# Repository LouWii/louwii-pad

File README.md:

# Louwii Pad

**Very basic USB macro pad for tinkering and experimenting.**

The main goal is to have it run a custom [QMK](https://docs.qmk.fm/) firmware, so that it can be easily programmed to be used as a macropad to help with day to day tasks. As it's running an ATmega32u4, same as the Arduino Leonardo & Micro, it can be programmed through the Arduino IDE as well, for even more customization.

![louwii-pad-rev1-small](https://private-user-images.githubusercontent.com/2750789/670247439-dfbe5354-9f28-458f-8513-f5d79d3b1d79.jpeg?jwt=eyJ0eXAiOiJKV1QiLCJhbGciOiJIUzI1NiJ9.eyJpc3MiOiJnaXRodWIuY29tIiwiYXVkIjoicmF3LmdpdGh1YnVzZXJjb250ZW50LmNvbSIsImtleSI6ImtleTUiLCJleHAiOjE3OTE2MDY3MzIsIm5iZiI6MTc5MTYwNjQzMiwicGF0aCI6Ii8yNzUwNzg5LzY3MDI0NzQzOS1kZmJlNTM1NC05ZjI4LTQ1OGYtODUxMy1mNWQ3OWQzYjFkNzkuanBlZz9YLUFtei1BbGdvcml0aG09QVdTNC1ITUFDLVNIQTI1NiZYLUFtei1DcmVkZW50aWFsPUFLSUFWQ09EWUxTQTUzUFFLNFpBJTJGMjAyNjEwMTAlMkZ1cy1lYXN0LTElMkZzMyUyRmF3czRfcmVxdWVzdCZYLUFtei1EYXRlPTIwMjYxMDEwVDA0MjcxMlomWC1BbXotRXhwaXJlcz0zMDAmWC1BbXotU2lnbmF0dXJlPTJkZTdlY2E2MmEyYmFmMzFiNmU4NDI2MTk5MDRmYjJjY2RkNmYwZjc5OTA3MTJlYjgzNDFjMWMxNGFiNTI4MTAmWC1BbXotU2lnbmVkSGVhZGVycz1ob3N0JnJlc3BvbnNlLWNvbnRlbnQtdHlwZT1pbWFnZSUyRmpwZWcifQ.r9Crihq03SLz5WYOTDRxo0ubDbzw7JnOoz72aCsSmFU)

![louwii-pad-rev1-demo](https://private-user-images.githubusercontent.com/2750789/670255763-4d714bb6-b55f-40b0-9e51-5dd4ab754735.gif?jwt=eyJ0eXAiOiJKV1QiLCJhbGciOiJIUzI1NiJ9.eyJpc3MiOiJnaXRodWIuY29tIiwiYXVkIjoicmF3LmdpdGh1YnVzZXJjb250ZW50LmNvbSIsImtleSI6ImtleTUiLCJleHAiOjE3OTE2MDgxOTMsIm5iZiI6MTc5MTYwNzg5MywicGF0aCI6Ii8yNzUwNzg5LzY3MDI1NTc2My00ZDcxNGJiNi1iNTVmLTQwYjAtOWU1MS01ZGQ0YWI3NTQ3MzUuZ2lmP1gtQW16LUFsZ29yaXRobT1BV1M0LUhNQUMtU0hBMjU2JlgtQW16LUNyZWRlbnRpYWw9QUtJQVZDT0RZTFNBNTNQUUs0WkElMkYyMDI2MTAxMCUyRnVzLWVhc3QtMSUyRnMzJTJGYXdzNF9yZXF1ZXN0JlgtQW16LURhdGU9MjAyNjEwMTBUMDQ1MTMzWiZYLUFtei1FeHBpcmVzPTMwMCZYLUFtei1TaWduYXR1cmU9ZWU5ZTIwNDVjZWY1OTQwN2Y3YzA2Nzk1MTAyMDU3NDMxMTI2N2RiNjA0Zjg4YjAwZTJkOWJiYTJjMjczZDJmOSZYLUFtei1TaWduZWRIZWFkZXJzPWhvc3QmcmVzcG9uc2UtY29udGVudC10eXBlPWltYWdlJTJGZ2lmIn0.mEn1UY_JDH-Clc5-bU8d7kEX9qx5xtZxYkt8m8s8BgE)

This demo is running the default QMK firmware. The bottom right knob is used to switch between layers, which get displayed on the OLED screen.

## Inspiration

* [ruiqimao's tutorial](https://github.com/ruiqimao/keyboard-pcb-guide)
* [Arisu](https://github.com/FateNozomi/arisu-pcb)
* [cpm43](https://github.com/Gtrx0/cpm43)
* [Gtrx0/Keyboard-template-atmega32u4](https://github.com/Gtrx0/Keyboard-template-atmega32u4)

[ATmega32u4 official doc](http://ww1.microchip.com/downloads/en/devicedoc/atmel-7766-8-bit-avr-atmega16u4-32u4_datasheet.pdf)

## BOM (list of components)

[See doc](BOM.md)

## Bootlader, ATmega flashing

Flash a bootloader, set the chip fuses: [See doc](ATMEGA.md)

## Firmware (QMK)

[See doc](FIRMWARE.md)

## Revisions

[See doc](REVISIONS.md)

## Third party libs

[See doc](LIBS.md)

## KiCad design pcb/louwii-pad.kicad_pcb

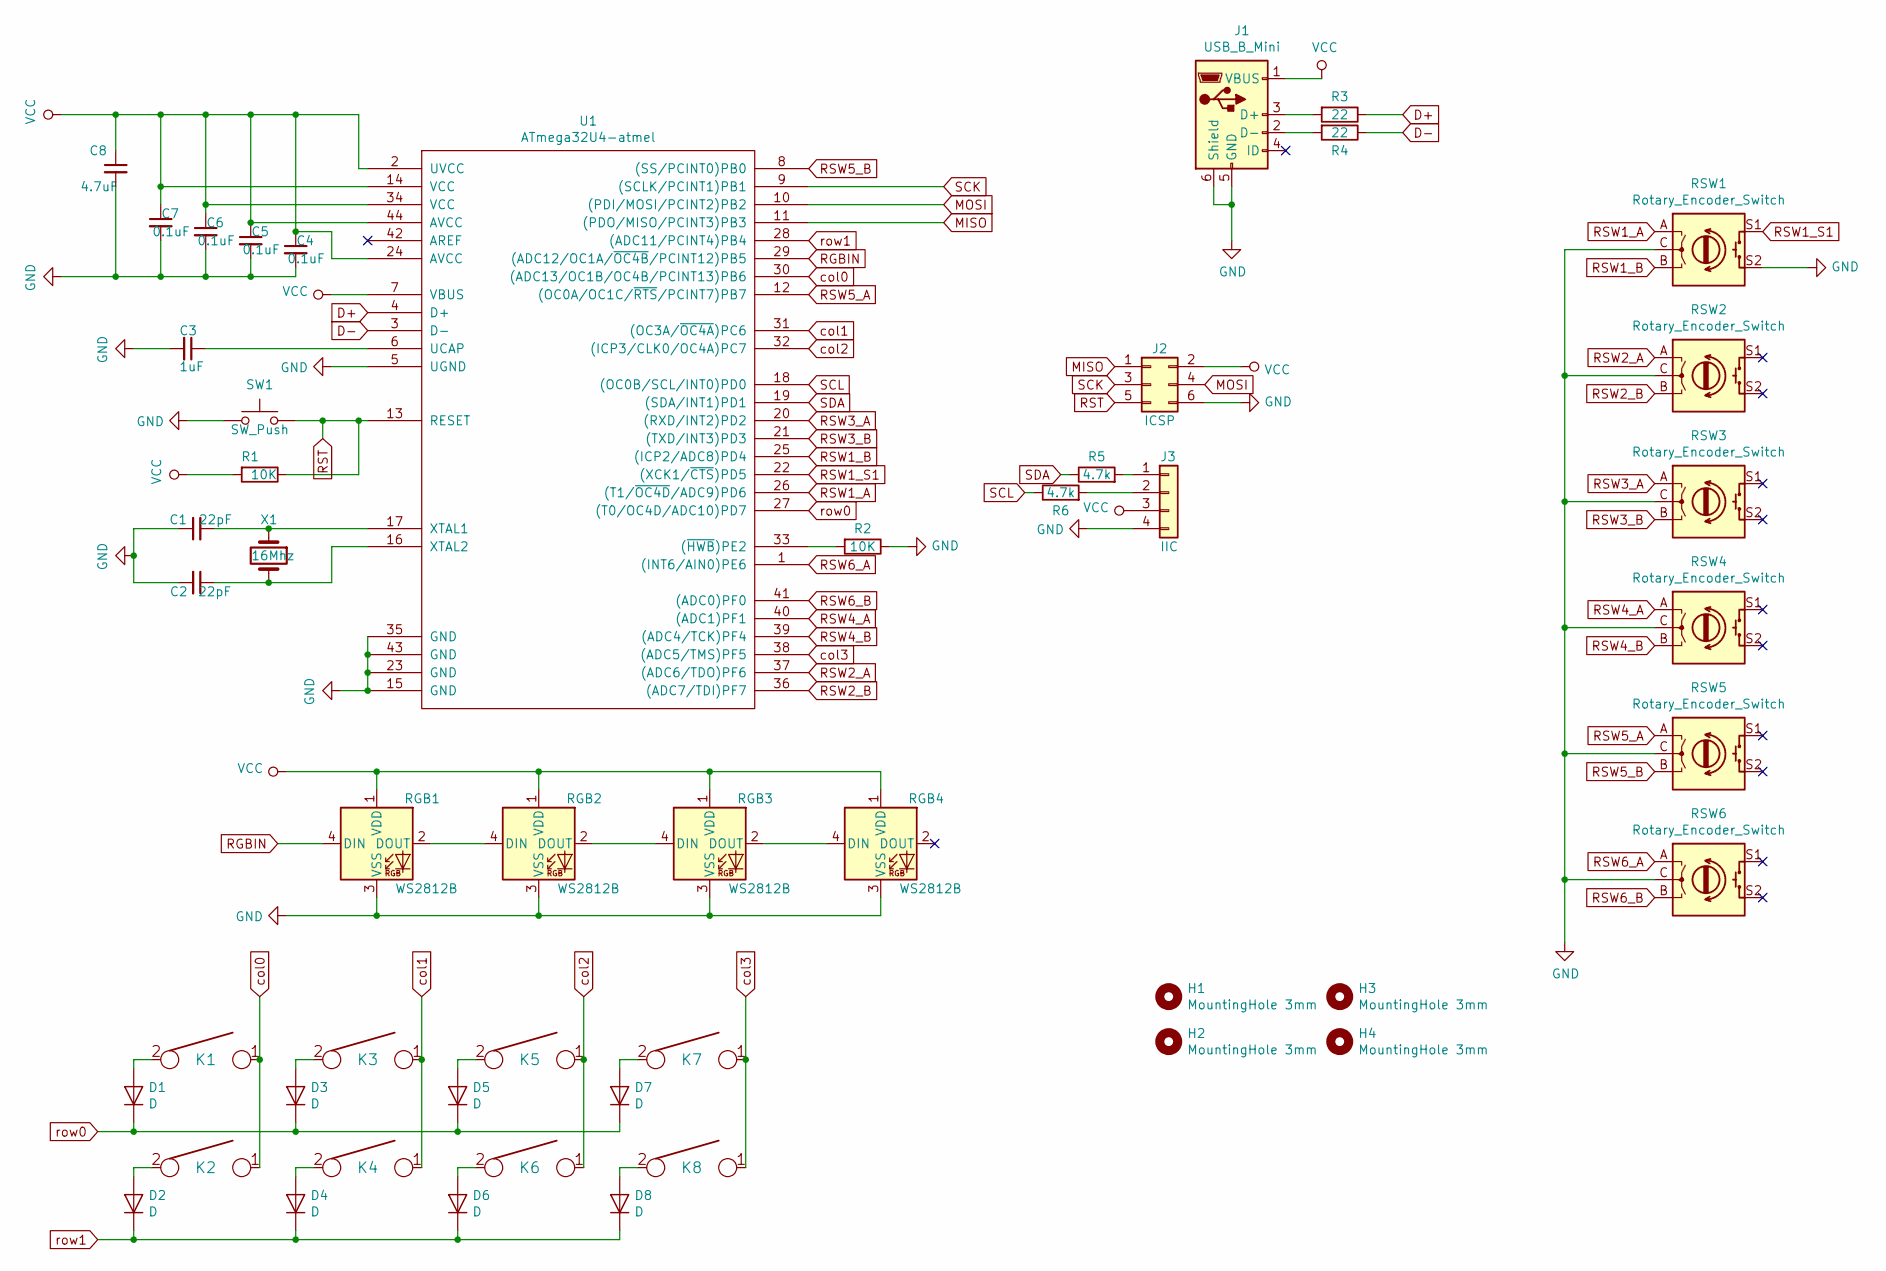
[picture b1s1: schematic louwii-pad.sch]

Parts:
C1, C2: 22pF; C_Disc_D4.3mm_W1.9mm_P5.00mm
C3: 1uF; C_Disc_D4.3mm_W1.9mm_P5.00mm
C4, C5, C6, C7: 0.1uF; C_Disc_D4.3mm_W1.9mm_P5.00mm
C8: 4.7uF; C_Radial_D5.0mm_H7.0mm_P2.00mm
D1, D2, D3, D4, D5, D6, D7, D8: D; D_DO-35_SOD27_P7.62mm_Horizontal
H1, H2, H3, H4: MountingHole 3mm; MountingHole_3.2mm_M3_ISO7380_Pad
J1: USB_B_Mini; USB_Mini-B_Lumberg_2486_01_Horizontal
J2: ICSP; PinHeader_2x03_P2.54mm_Vertical
J3: IIC; PinHeader_1x04_P2.54mm_Vertical
K1, K2, K3, K4, K5, K6, K7, K8: KEYSW; MX_PCB_100H
R1, R2: 10K; R_Axial_DIN0207_L6.3mm_D2.5mm_P10.16mm_Horizontal
R3, R4: 22; R_Axial_DIN0207_L6.3mm_D2.5mm_P10.16mm_Horizontal
R5, R6: 4.7k; R_Axial_DIN0207_L6.3mm_D2.5mm_P10.16mm_Horizontal
RGB1, RGB2, RGB3, RGB4: WS2812B; WS2812b
RSW1, RSW2, RSW3, RSW4, RSW5, RSW6: Rotary_Encoder_Switch; RotaryEncoder_Alps_EC11E-Switch_Vertical_H20mm
SW1: SW_Push; SW_SPST_TL3342
U1: ATmega32U4-atmel; TQFP-44_10x10mm_P0.8mm
X1: 16Mhz; Crystal_HC49-U_Vertical

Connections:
D+: R3.1, U1.4 (D+)
D-: R4.1, U1.3 (D-)
GND: C1.1, C2.2, C3.2, C4.2, C5.2, C6.2, C7.2, C8.2, J1.5 (GND), J1.6 (Shield), J2.6, J3.4, R2.1, RGB1.3 (VSS), RGB2.3 (VSS), RGB3.3 (VSS), RGB4.3 (VSS), RSW1.C, RSW1.S2, RSW2.C, RSW3.C, RSW4.C, RSW5.C, RSW6.C, SW1.1, U1.5 (UGND), U1.15 (GND), U1.23 (GND), U1.35 (GND), U1.43 (GND)
MISO: J2.1, U1.11 ((PDO/MISO/PCINT3)PB3)
MOSI: J2.4, U1.10 ((PDI/MOSI/PCINT2)PB2)
unnamed: C1.2, U1.17 (XTAL1), X1.1
unnamed: C2.1, U1.16 (XTAL2), X1.2
unnamed: C3.1, U1.6 (UCAP)
unnamed: D1.2 (A), K1.2
unnamed: D2.2 (A), K2.2
unnamed: D3.2 (A), K3.2
unnamed: D4.2 (A), K4.2
unnamed: D5.2 (A), K5.2
unnamed: D6.2 (A), K6.2
unnamed: D7.2 (A), K7.2
unnamed: D8.2 (A), K8.2
unnamed: J1.2 (D-), R4.2
unnamed: J1.3 (D+), R3.2
unnamed: J3.1, R5.2
unnamed: J3.2, R6.2
unnamed: R2.2, U1.33 ((~HWB~)PE2)
unnamed: RGB1.2 (DOUT), RGB2.4 (DIN)
unnamed: RGB2.2 (DOUT), RGB3.4 (DIN)
unnamed: RGB3.2 (DOUT), RGB4.4 (DIN)
RGBIN: RGB1.4 (DIN), U1.29 ((ADC12/OC1A/~OC4B~/PCINT12)PB5)
RST: J2.5, R1.1, SW1.2, U1.13 (RESET)
RSW1_A: RSW1.A, U1.26 ((T1/~OC4D~/ADC9)PD6)
RSW1_B: RSW1.B, U1.25 ((ICP2/ADC8)PD4)
RSW1_S1: RSW1.S1, U1.22 ((XCK1/~CTS~)PD5)
RSW2_A: RSW2.A, U1.37 ((ADC6/TDO)PF6)
RSW2_B: RSW2.B, U1.36 ((ADC7/TDI)PF7)
RSW3_A: RSW3.A, U1.20 ((RXD/INT2)PD2)
RSW3_B: RSW3.B, U1.21 ((TXD/INT3)PD3)
RSW4_A: RSW4.A, U1.40 ((ADC1)PF1)
RSW4_B: RSW4.B, U1.39 ((ADC4/TCK)PF4)
RSW5_A: RSW5.A, U1.12 ((OC0A/OC1C/~RTS~/PCINT7)PB7)
RSW5_B: RSW5.B, U1.8 ((SS/PCINT0)PB0)
RSW6_A: RSW6.A, U1.1 ((INT6/AIN0)PE6)
RSW6_B: RSW6.B, U1.41 ((ADC0)PF0)
SCK: J2.3, U1.9 ((SCLK/PCINT1)PB1)
SCL: R6.1, U1.18 ((OC0B/SCL/INT0)PD0)
SDA: R5.1, U1.19 ((SDA/INT1)PD1)
VCC: C4.1, C5.1, C6.1, C7.1, C8.1, J1.1 (VBUS), J2.2, J3.3, R1.2, RGB1.1 (VDD), RGB2.1 (VDD), RGB3.1 (VDD), RGB4.1 (VDD), U1.2 (UVCC), U1.7 (VBUS), U1.14 (VCC), U1.24 (AVCC), U1.34 (VCC), U1.44 (AVCC)
col0: K1.1, K2.1, U1.30 ((ADC13/OC1B/OC4B/PCINT13)PB6)
col1: K3.1, K4.1, U1.31 ((OC3A/~OC4A~)PC6)
col2: K5.1, K6.1, U1.32 ((ICP3/CLK0/OC4A)PC7)
col3: K7.1, K8.1, U1.38 ((ADC5/TMS)PF5)
row0: D1.1 (K), D3.1 (K), D5.1 (K), D7.1 (K), U1.27 ((T0/OC4D/ADC10)PD7)
row1: D2.1 (K), D4.1 (K), D6.1 (K), D8.1 (K), U1.28 ((ADC11/PCINT4)PB4)

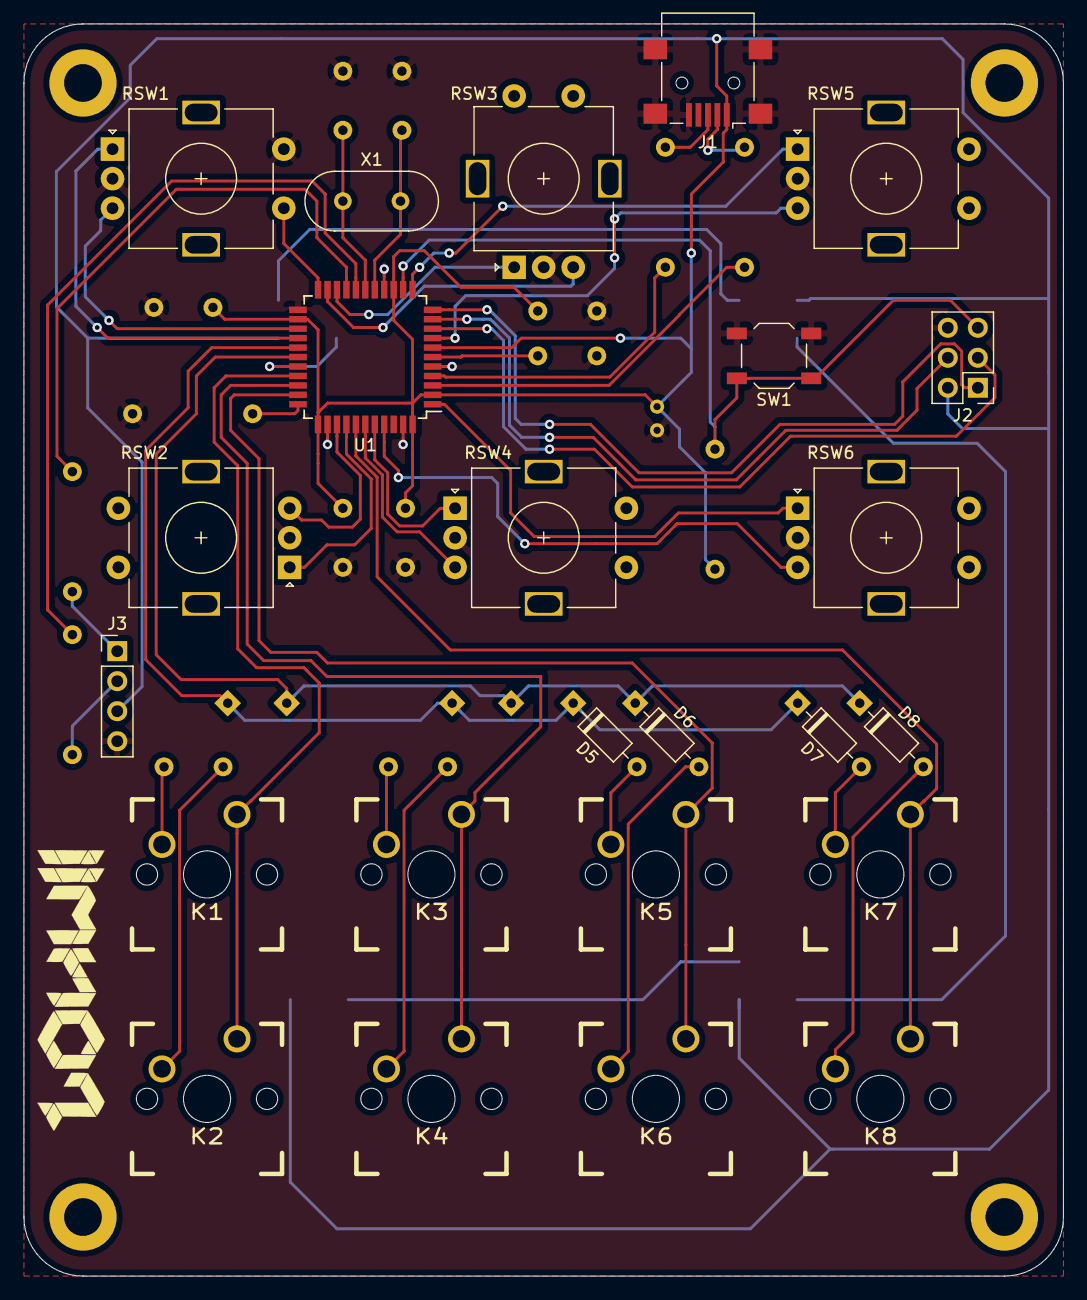
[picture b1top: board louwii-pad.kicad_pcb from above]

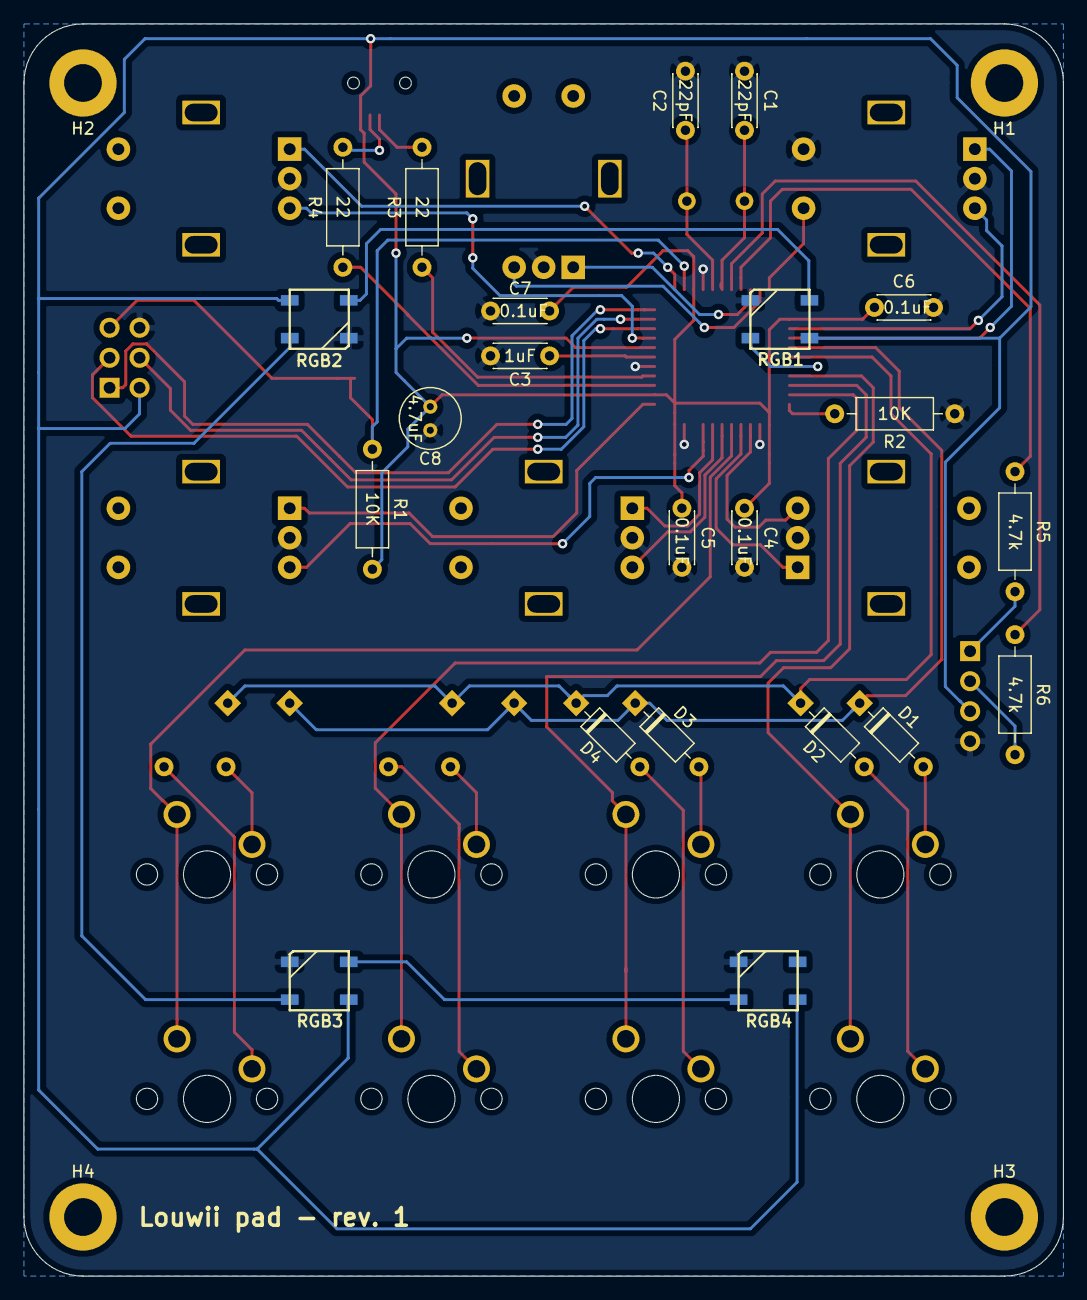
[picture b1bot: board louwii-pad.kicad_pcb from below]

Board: 2 copper layers, 88.0 x 106.0 mm, 50 parts (22 on the bottom side), 49 nets.

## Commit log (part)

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2019-10-24 add readme
2019-10-24 Update readme with links
2019-10-24 add WIP pcb schematics
2019-10-24 add RGB leds - WIP
2019-10-25 add more links and info in README
2019-10-25 Finished PCB schematics
2019-10-25 fix component ids
2019-10-25 finish up schematics and start PCB design
2019-10-26 add BOM
2019-10-26 update schematics, update net, update footprints, update pcb design with missing footprints
2019-10-27 Add list of third party libs
2019-10-27 add more 3d models, finish up PCB tracing
2019-10-28 finish up tracing, updating footprints, adding 3d models
2019-10-28 cleanup silk layers
2019-10-29 add logo and rev on PCB
2019-10-29 add gerber files
2019-10-30 update all docs
2019-11-16 add schema PDF export
2019-11-18 Add doc about flashing blank ATmega
2019-11-22 Add more blablabla
2020-02-16 fix doc files
2020-02-16 add picture of rev1 completed
2021-01-21 Minor text updates
2024-03-03 Update FIRMWARE.md
    Add direct link to louwii-pad firmware source files
2024-03-03 Docs changes
